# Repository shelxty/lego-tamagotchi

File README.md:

# Lego Tamagotchi!

This is a tamagotchi (a virtual pet) modeled after a lego piece! Created for Hack Club's #Fallout YSWS. It's my first larger-scale hardware project! 

_He says hello! And also asks you to help him find a name! (Because I'm not creative)_

## Motivation 
As a complete beginner in hardware, I was absolutely lost on what hardware was. I had looked at a few KiCad tutorials, but each time I was confused -- what the hell was ground? What's the difference between 5V and 3.3V? Why are some things wired like that? But on a trip back from NYC with Tanishq, he gave me a good explanation on what hardware was, and how to get started with it. I was surprised to hear that he made his very own full-fleshed tutorial for those beginning in hardware, and honestly, I'll credit Tanishq and this tutorial for truly teaching me what hardware is. I'm still a beginner, but at least I've made that first step from zero to... one! Yay! 

Anyways, this is my first completed hardware project that uses both PCBs and CAD. Thank you Tanishq! 

## How It Works / How It's Used

### Components: 

| **Designator** | **Part** | **Wiring** | **Purpose** |
|-------|---|-------|---------------|
| U1 | Seeed Studio XIAO ESP32-C3 | N/A | Made by Seeed Studio, it's a miniature ESP32 that uses a USB-C for power; it's a microcontroller capable of WiFi and Bluetooth. Everything else on the PCB gives this module inputs, outputs, and power | 
| BT1 | Single-cell battery | N/A | This powers the whole board, connected to the XIAO BATT+ charging input pins | 
| SW1 , SW2, SW3 | 3 push buttons | GPIO2 (D0), GPIO3 (D1), and GPIO4 (D2), respectively | These push buttons allow the user to interact with the tamagotchi | 
| U2 | 0.96 inch OLED display (SSD1315) | SDA is wired to GPIO6 (D4) and SCL is wired to GPIO7 (D5), while VCC takes in 3.3V | This is the display for the pet -- it's the area that allows you to actually play and interact with your tamagotchi | 
| BUZZER1 | A piezoelectric buzzer | GPIO10 (D10) (MOSI) | This is the sound output. Whenever you press an action, the tamagotchi responds by buzzing with the buzzer to provide feedback. |

### Hardware: 

- **Tool:** KiCad 10
- **Board:** 2-layer PCB with a custom outline
- **Microcontroller:** The Seeed Studio XIAO ESP32-C3
- **Display:** A 0.96" 128x64 OLED display with a SSD1315 driver
- **Audio:** A piezoelectric buzzer approximately 12 millimeters in diameter
- **Input:** 3 push buttons embedded onto the PCB 

---

_My zine!_

---
## PCB Design

_View of the schematic_

_View of the PCB (if you notice the little design in the middle, you should dm me on slack @shelx with a Matt Rose furby picture)_

_3D view_ 

...furbies...

anyways! 

---
## CAD 

This tamagotchi project got me to finally start learning how to CAD so wow! 

|  |  | 
|---|---| 
| Exploded View | Frontal View | 
|  |  | 
| Back View | Side (Right) View |

The PCB is screwed in after the 3D printing is finished. 

Link to Onshape document: https://cad.onshape.com/documents/e4a64d821d7c72313f05382f/w/889a245c2565bee9629b9436/e/a5b00448e143d248d84f17b3?renderMode=0&uiState=6a3da3ea25405d2bf4fc1bb7

To try it out, use the Wokwi simulator: https://wokwi.com/projects/467841668828380161

### Measurements (for 3D printing)

This should be able to be printed with a Bambu A1 mini! 
**Context:** A Bambu A1 mini bed size is 180mm x 180mm x 180mm.

- Leg: 120mm (height) x 64mm (length)
- Torso: 131mm (height) x 137mm (longest base) 
- Head: 43mm (height), 91mm (diameter)

---

## Bill of Materials (BOM) 

| Item |	Description |	Reference |	Qty |	MOQ |	Value |	Per Unit Price ($) |	Total Price ($) |	Footprint |	MPN |	URL |
|------|--------------|-----------|-----|-----|-------|--------------------|------------------|-----------|-----|-----|
| Battery |	Single-cell battery |	BT1 |	1 |	1 |	Battery_Cell |	3.87 |	3.87 |	Connector_PinHeader_2.54mm:PinHeader_1x02_P2.54mm_Vertical |	N/A |	[Link](https://www.aliexpress.us/item/3256808925172396.html?spm=a2g0o.productlist.main.11.6e1523a2T5o5mT&algo_pvid=a7f5d709-8287-4bd9-877e-4b7454d07aea&algo_exp_id=a7f5d709-8287-4bd9-877e-4b7454d07aea-10&pdp_ext_f=%7B%22order%22%3A%22115%22%2C%22eval%22%3A%221%22%2C%22fromPage%22%3A%22search%22%7D&pdp_npi=6%40dis%21USD%215.38%213.87%21%21%2136.32%2126.15%21%4021032f3717820018898186181ef57d%2112000047954562112%21sea%21US%217756416958%21X%211%210%21n_tag%3A-29911%3Bd%3A882c3b75%3Bm03_new_user%3A-29895&curPageLogUid=gVBhZCgn1w6G&utparam-url=scene%3Asearch%7Cquery_from%3A%7Cx_object_id%3A1005009111487148%7C_p_origin_prod%3A) |
| Buzzer |	Audio buzzer |	BUZZER1 |	1 |	10 |	1207-P6.5MM |	0.0572 |	0.57 |	easyeda2kicad:BUZ-TH_BD12.5-P6.50-D1.4 |	1207-P6.5MM |	[Link](https://www.lcsc.com/product-detail/C49246964.html?s_z=s_p_1207-P6.5MM&spm=wm.fly.bg.0.xh&lcsc_vid=QQVaAVJeTlJdUVBVE1hcBVFWEwcNBVxeQwAPA1YHFQMxVlNeRVFeVVRXQ1laUDsOAxUeFF5JWBYZEEoKFBINSQcJGk4dAgUUFAk%3D) |
| Buttons |	Push button switch, generic, two pins |	SW1,SW2,SW3 |	3 |	10 |	SW_Push |	0.053 |	0.53 |	easyeda2kicad:SW-TH_4P-L4.5-W4.5-P3.00-LS4.8 |	TS-1088-AR02016 |	[Link](https://www.lcsc.com/product-detail/C720477.html?s_z=s_q_p_PUSH%2520BUTTON%2520SWITCH&spm=wm.ssy.bg.0.xh&lcsc_vid=QQVaAVJeTlJdUVBVE1hcBVFWEwcNBVxeQwAPA1YHFQMxVlNeRVFeVVRfQVlaXzsOAxUeFF5JWBYZEEoKFBINSQcJGk4NBhADEA4cHktfQVlADxALGw%3D%3D) |
| MCU |	XIAO-ESP32-C3 |	U1 |	1 |	1 |	XIAO-ESP32-C3-SMD |	2.95 |	2.95 |	Seeed_Studio_XIAO_Series:XIAO-ESP32-C3-SMD |	N/A |	[Link](https://www.aliexpress.us/item/3256808694624250.html?spm=a2g0o.productlist.main.2.7bf11671FvH8Ua&algo_pvid=71c252e5-18c7-4c17-801d-9350ae77c1f5&algo_exp_id=71c252e5-18c7-4c17-801d-9350ae77c1f5-1&pdp_ext_f=%7B%22order%22%3A%22718%22%2C%22eval%22%3A%221%22%2C%22fromPage%22%3A%22search%22%7D&pdp_npi=6%40dis%21USD%217.34%212.95%21%21%2149.50%2119.89%21%402101e62517820022180805568ecf92%2112000047069200692%21sea%21US%217756416958%21X%211%210%21n_tag%3A-29911%3Bd%3A882c3b75%3Bm03_new_user%3A-29895%3BpisId%3A5000000209196075&curPageLogUid=46Mmlu4FUmrg&utparam-url=scene%3Asearch%7Cquery_from%3A%7Cx_object_id%3A1005008880939002%7C_p_origin_prod%3A) |
| OLED Display |	Display screen |	U2 |	1 |	1 |	HS96L03W2C03 |	2.24 |	2.24 |	easyeda2kicad:OLED-TH_L27.8-W27.2-P2.54_C9900033791 |	HS96L03W2C03 |	[Link](https://www.lcsc.com/product-detail/C5248080.html?s_z=n_q_HS96L03W2C03&spm=wm.fly.bg.0.xh&lcsc_vid=QQVaAVJeTlJdUVBVE1hcBVFWEwcNBVxeQwAPA1YHFQMxVlNeRVFeVl1TQFBZUzsOAxUeFF5JWBYZEEoKFBINSQcJGk4dAgUUFAk%3D)
| PCB Build |	JLCPCB |	N/A |	1 |	1 |	N/A |	2 |	2 |	N/A |	N/A |	N/A |
| PCB Shipping |	JLCPCB |	N/A |	1 |	1 |	N/A |	2.5 |	2.5 |	N/A |	N/A |	N/A |
| Total |		| |	9 |	25	|	|	| 14.66			

Credits: 
- For the tutorial: [@TaniWanKenobi's](https://github.com/TaniWanKenobi) tamagotchi guide [linked here](https://fallout.hackclub.com/docs/guided-projects/tamagotchi) (it's amazing!)
- A screw import: https://grabcad.com/library/screw-06-1
- Hack Club Fallout mentors!

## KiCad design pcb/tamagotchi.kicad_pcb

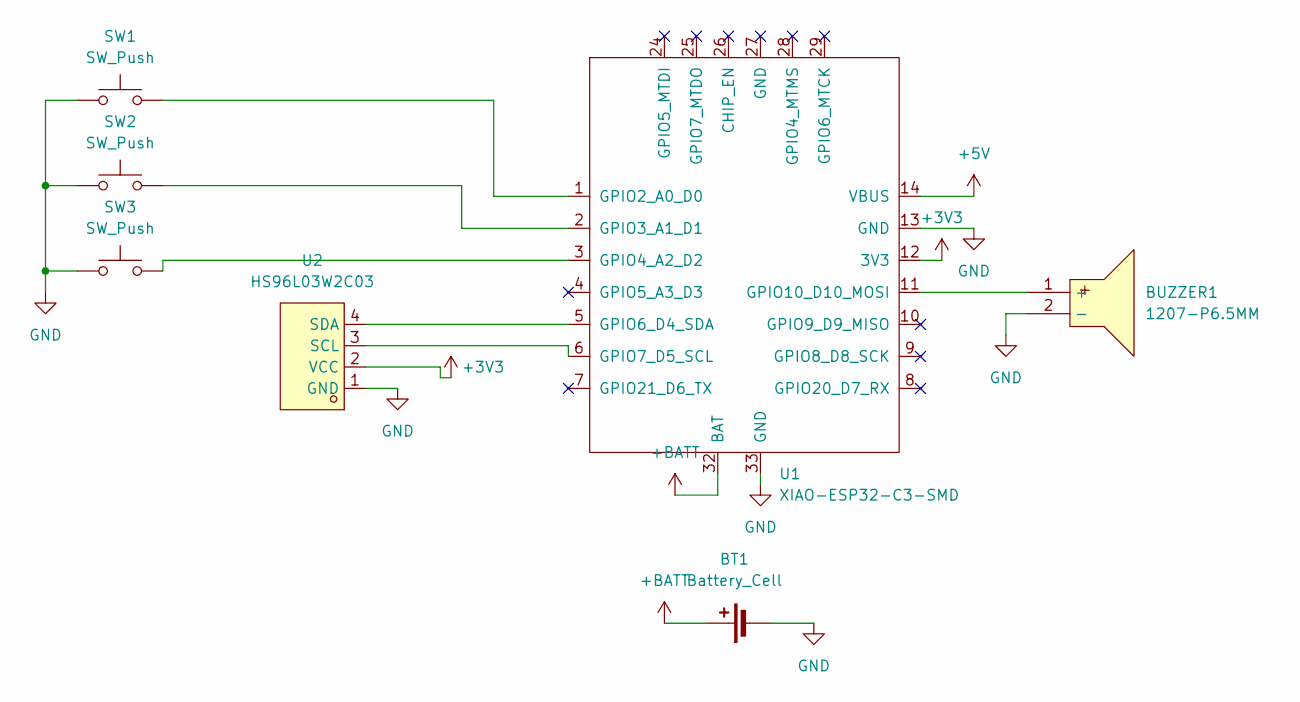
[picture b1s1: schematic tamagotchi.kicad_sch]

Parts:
BT1: Battery_Cell; PinHeader_1x02_P2.54mm_Vertical
BUZZER1: 1207-P6.5MM; BUZ-TH_BD12.5-P6.50-D1.4; MPN 1207-P6.5MM; LCSC Part C49246964
SW1, SW2, SW3: SW_Push; SW-TH_4P-L4.5-W4.5-P3.00-LS4.8
U1: XIAO-ESP32-C3-SMD
U2: HS96L03W2C03; OLED-TH_L27.8-W27.2-P2.54_C9900033791; MPN HS96L03W2C03; LCSC Part C5248080

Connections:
+3V3: U1.12 (3V3), U2.2 (VCC)
+5V: U1.14 (VBUS)
+BATT: BT1.1 (+), U1.32 (BAT)
GND: BT1.2 (-), BUZZER1.2 (-), SW1.1, SW2.1, SW3.1, U1.13 (GND), U1.33 (GND), U2.1 (GND)
unnamed: BUZZER1.1 (+), U1.11 (GPIO10_D10_MOSI)
unnamed: SW1.2, U1.1 (GPIO2_A0_D0)
unnamed: SW2.2, U1.2 (GPIO3_A1_D1)
unnamed: SW3.2, U1.3 (GPIO4_A2_D2)
unnamed: U1.5 (GPIO6_D4_SDA), U2.4 (SDA)
unnamed: U1.6 (GPIO7_D5_SCL), U2.3 (SCL)

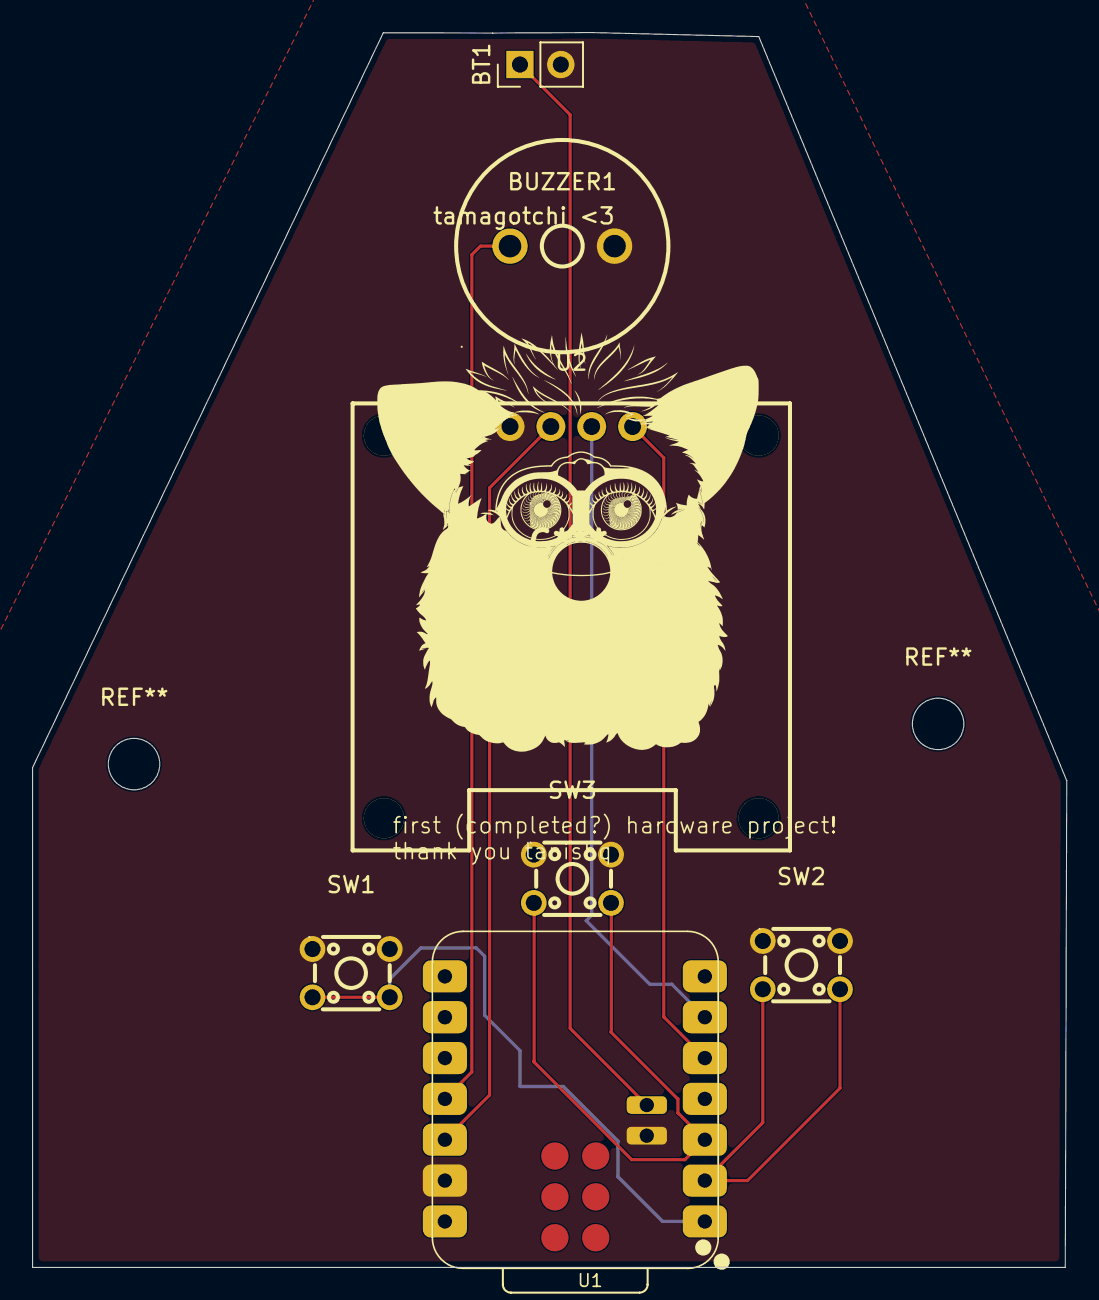
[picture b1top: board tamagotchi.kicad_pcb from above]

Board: 2 copper layers, 64.3 x 76.8 mm, 7 parts (0 on the bottom side), 9 nets.

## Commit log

2026-06-09 redid some routing and added a furby design because i keep thinking of matt rose furbies when i see tamagotchi
2026-06-20 version control for egg tamagotchi
2026-06-20 finished routing and fixed DRC errors
2026-06-20 fixed up some really dumb xiao-esp32 issues (namely with the button numbers being wrong
2026-06-21 currently working on my readme
    adfasdf
2026-06-21 added zine asd;laf
    yum
2026-06-21 updated zine
    oops
2026-06-21 BOM
    bom bom bom!
2026-06-21 renamed bom to bom
2026-06-21 uploaded zine pdf
2026-06-21 Create tamagotchi
2026-06-21 Delete CAD/tamagotchi
    oops
2026-06-21 added some more stuff to readme for the pcb
2026-06-21 a
    a
2026-06-24 updated bom
2026-06-24 Rename fp-info-cache to pcb/fp-info-cache
2026-06-24 Rename fp-lib-table to pcb/fp-lib-table
2026-06-24 Rename sym-lib-table to pcb/sym-lib-table
2026-06-24 Rename tamagotchi-gencad.cad to CAD/tamagotchi-gencad.cad
2026-06-24 Rename tamagotchi.kicad_pcb to pcb/tamagotchi.kicad_pcb
2026-06-24 Rename tamagotchi.kicad_pro to pcb/tamagotchi.kicad_pro
2026-06-24 Rename tamagotchi.kicad_sch to pcb/tamagotchi.kicad_sch
2026-06-24 Rename gerbers.zip to pcb/gerbers.zip
2026-06-25 Add link to Onshape document in README
    Added a link to the Onshape document for reference.
2026-06-25 Rename gerbers.zip to production/gerbers.zip
2026-06-25 moved footprints and symbols over to the Library folder
    to make it all more organized
2026-06-27 Create a
2026-06-27 wokwi simulation files
2026-06-27 Include Wokwi simulator link in README
    Added a link to the Wokwi simulator for testing.
2026-06-28 edited pcb and added THT holes
2026-06-28 Rename tamagotchi.kicad_prl to pcb/tamagotchi.kicad_prl
2026-06-28 Add 3D printing measurements to README
    Added measurements for 3D printing specifications including leg, torso, and head dimensions.
